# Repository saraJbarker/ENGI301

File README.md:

<h1>ENGI301</h1>
Repository for ENGI301 course work
<h3>Project 1</h3>
The project_1 folder contains the code for the PocketBeagle Medication Dispenser, found on my Hackster: https://www.hackster.io/sarajbarker/pocketbeagle-medication-dispenser-ca1f8f </br> </br>
All of the hardware can be found on the Hackster page. For the code, the only file needed is <a href=https://github.com/saraJbarker/ENGI301/blob/main/project_1/main_code3.py"">main_code3.py</a>. 
To set up and run this code: </br>
<ol>
  <li> Wire everything up according to the directions on Hackster (also see <a href="https://github.com/saraJbarker/ENGI301/blob/main/project_1/sketch_bb.png"> sketch_bb.png</a> for a Fritzing diagram) </li>
  <li> Connect the PocketBeagle to the internet </li>
  <li> Set up the PocketBeagle to run Python: 
    <ul>
      <li><code>sudo apt-get update </code></li>
      <li><code>sudo apt-get install build-essential python-dev python-setuptools python-smbus -y </code></li>
      <li><code>sudo apt-get install python-pip python3-pip -y</code></li>
    </ul>
  <li>Install Adafruit BBIO:
    <ul><code>sudo pip3 install --upgrade Adafruit_BBIO</code></ul>
    </li>
  <li>Drag and drop <a href=https://github.com/saraJbarker/ENGI301/blob/main/project_1/main_code3.py>main_code3.py</a> into your PocketBeagle directory.</li>
  <li>Press "Run".</li>
  </ol>
  </br>
  Included in the Project 1 folder are the STL and Solidworks files for the pillbox - the STL can go into a 3D printing software like 3DprinterOS, or you can modify the Solidworks file and make a new STL file. <a href="https://github.com/saraJbarker/ENGI301/blob/main/project_1/boxv3all.ai">boxv3all.ai</a> is the Illustrator file for the sides of the wooden box. This can be used with a laser cutter to cut the wood out. <a href="https://github.com/saraJbarker/ENGI301/blob/main/project_1/sketch_bb.png">sketch_bb.png</a> is a picture of the Fritzing file. <code>code_skeleton</code>, <code>main_code.py</code>, and <code>main_code2.py</code> are just in progress versions of the currently updated code, <code>main_code3.py</code> - there isn't a need to download these.
  <h3>Project 2</h3>
  The project_2 folder contains files for a PCB that would control the medication dispenser described in Project 1. The library, schematic, and board files in EAGLE are included in the EAGLE subfolder, and the Gerber files are in the MFG subfolder. If you would like to make this PCB, you will need to send the Gerber files to a manufacturer. There is also a PDF version of the schematic and a Bill of Materials inside the project_2 folder. </br>
  <i>Note:</i> the PCB has not been physically made, so there may be errors in the provided files.

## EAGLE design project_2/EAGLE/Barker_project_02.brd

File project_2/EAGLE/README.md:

This is the folder for all EAGLE files for the PCB.

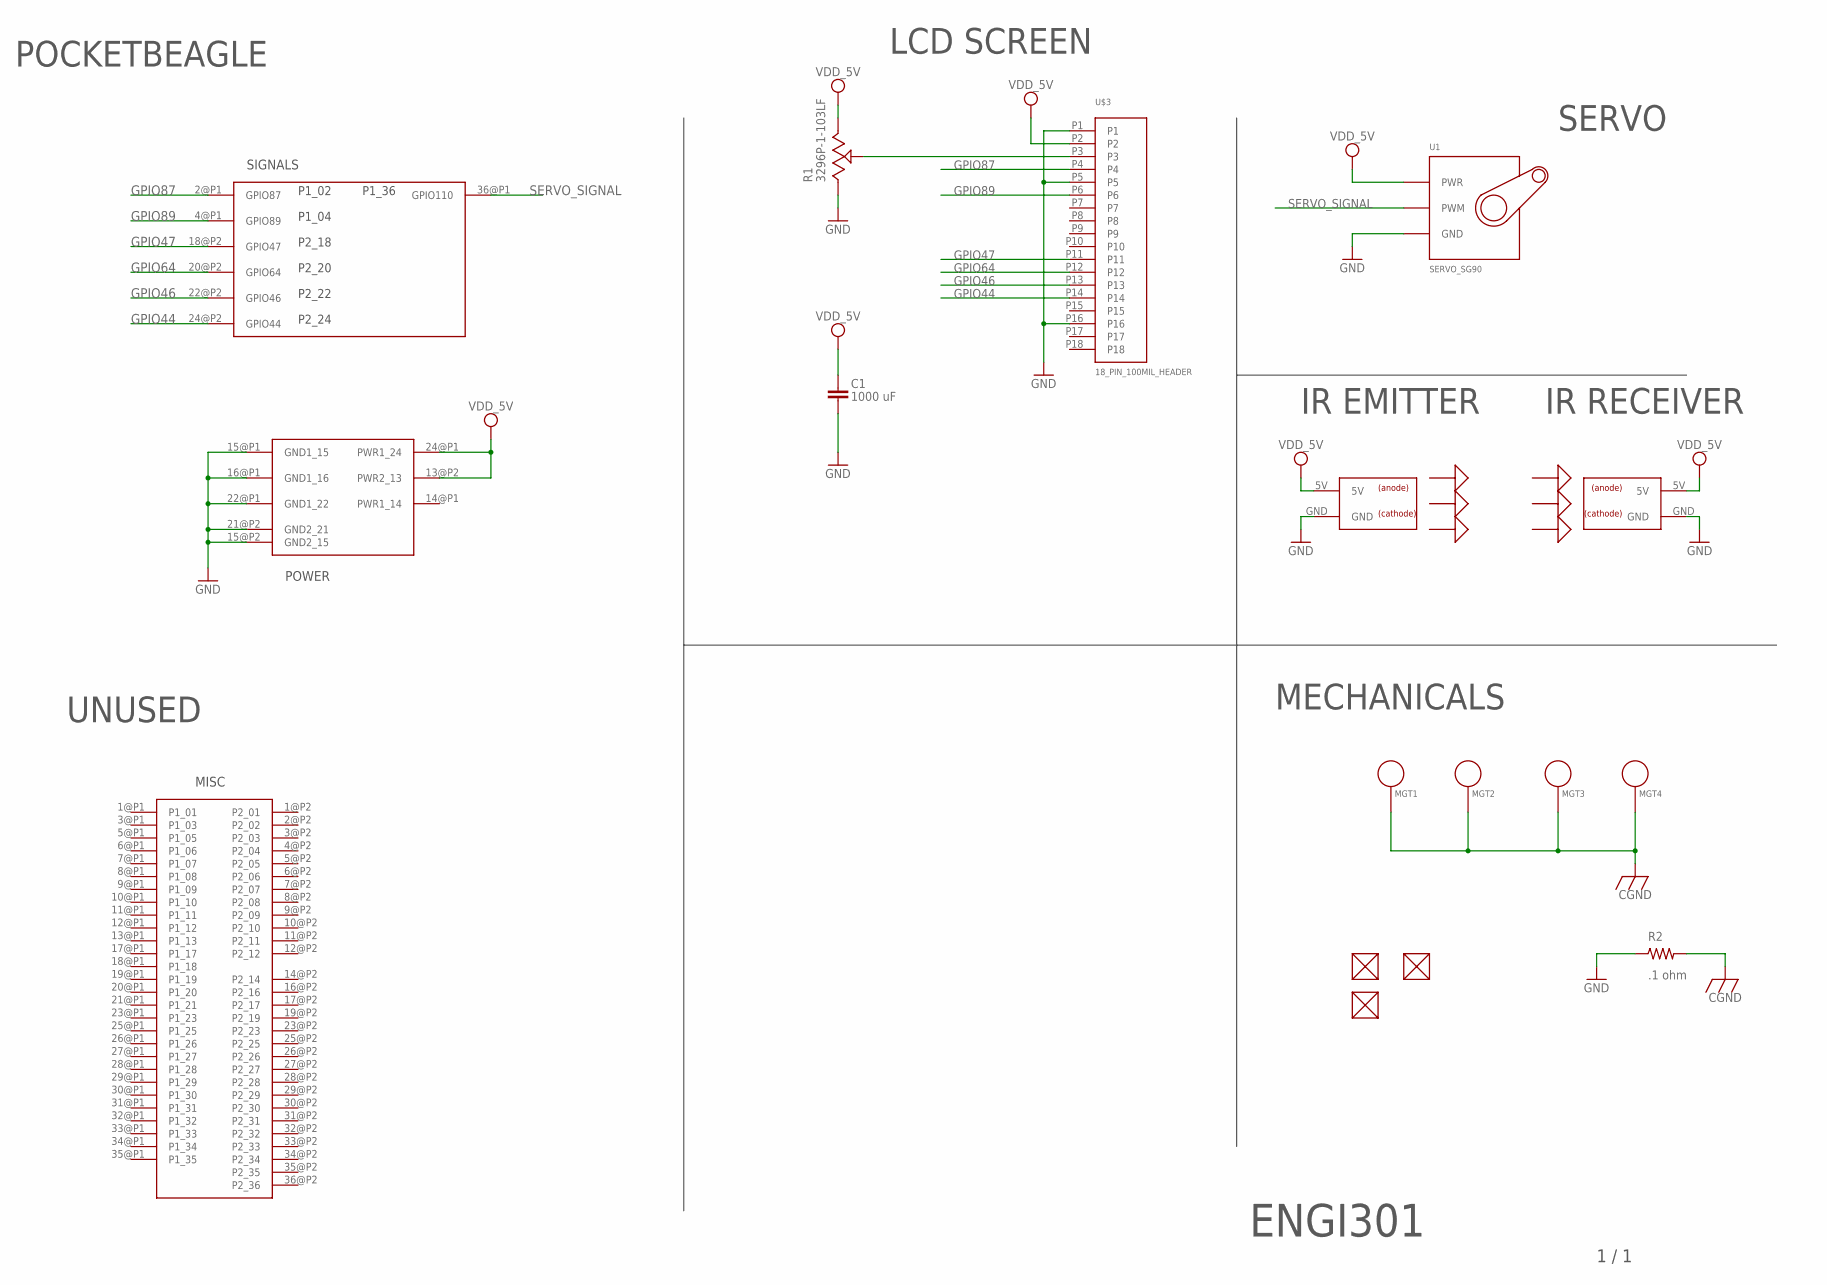
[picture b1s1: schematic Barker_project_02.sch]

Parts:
C1: 1000 uF; C0402
FUD1, FUD2, FUD3: FIDUCIAL; FIDUCIAL_40MIL
MGT1, MGT2, MGT3, MGT4: MOUNTING_HOLE
R1: 3296P-1-103LF; TRIM_3296P-1-103LF
R2: .1 ohm; R0402
U1: SERVO_SG90; SERVO-X1
U2: POCKETBEAGLE
U3: IR_EMITTER; 2_PIN_100MIL_HEADER
U4: IR_DETECTOR; 2_PIN_100MIL_HEADER
U$3: 18_PIN_100MIL_HEADER

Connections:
CGND: MGT1.P$1, MGT2.P$1, MGT3.P$1, MGT4.P$1, R2.2
GND: C1.2, R1.1 (CCW), R2.1, U1.GND, U2.15@P1 (GND1_15), U2.15@P2 (GND2_15), U2.16@P1 (GND1_16), U2.21@P2 (GND2_21), U2.22@P1 (GND1_22), U3.GND, U4.GND, U$3.P1, U$3.P5, U$3.P16
GPIO44: U2.24@P2 (GPIO44), U$3.P14
GPIO46: U2.22@P2 (GPIO46), U$3.P13
GPIO47: U2.18@P2 (GPIO47), U$3.P11
GPIO64: U2.20@P2 (GPIO64), U$3.P12
GPIO87: U2.2@P1 (GPIO87), U$3.P4
GPIO89: U2.4@P1 (GPIO89), U$3.P6
unnamed: R1.2 (WIPER), U$3.P3
SERVO_SIGNAL: U1.SIG (PWM), U2.36@P1 (GPIO110)
VDD_5V: C1.1, R1.3 (CW), U1.PWR, U2.13@P2 (PWR2_13), U2.24@P1 (PWR1_24), U3.5V, U4.5V, U$3.P2

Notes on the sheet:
IR RECEIVER
IR EMITTER
SERVO
LCD SCREEN
POCKETBEAGLE
MECHANICALS
POWER
SIGNALS
MISC
ENGI301
1 / 1
UNUSED

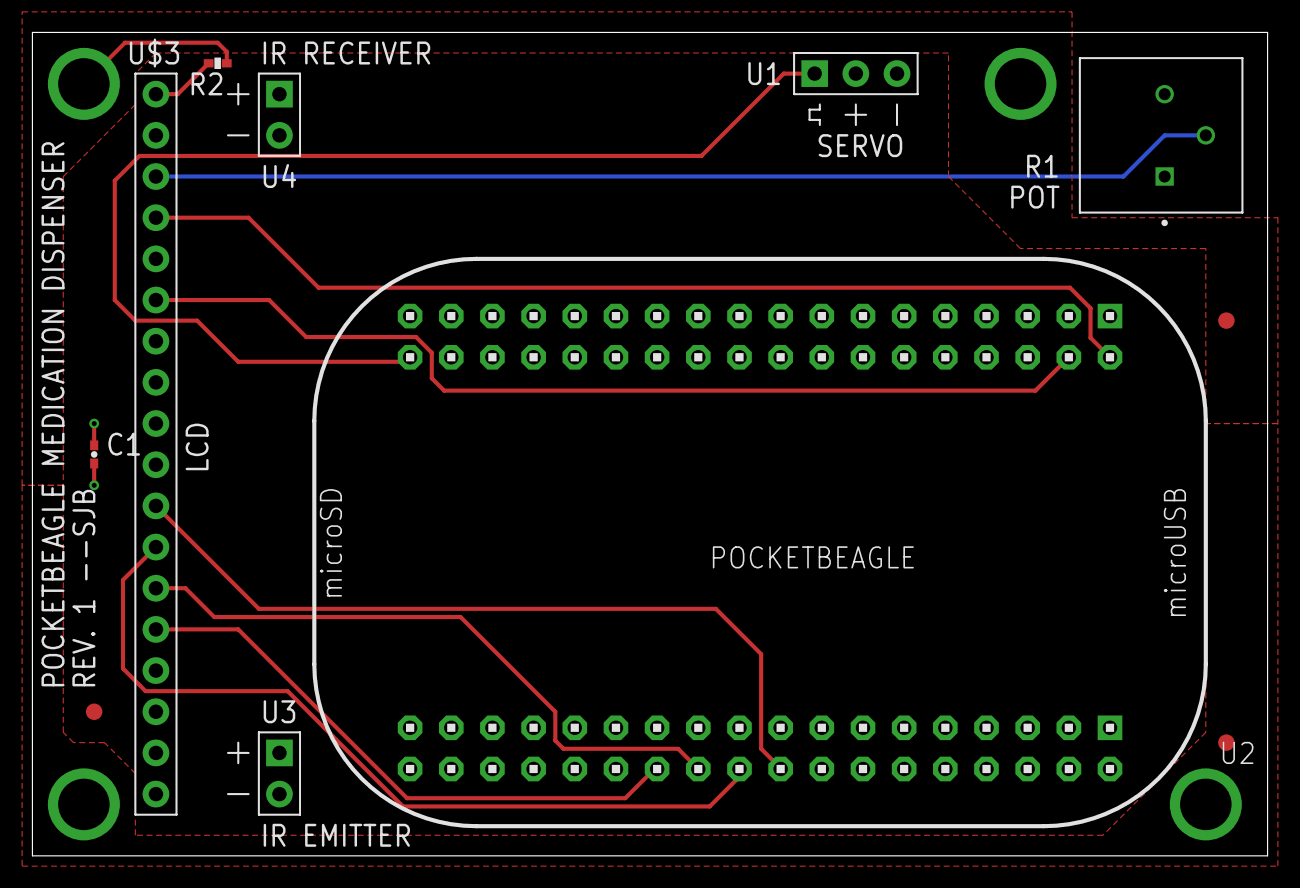
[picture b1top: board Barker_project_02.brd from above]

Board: 4 copper layers, 76.2 x 50.8 mm, 15 parts (0 on the bottom side), 11 nets.

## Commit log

2022-02-01 Updating README.md
2022-02-15 Added simple calc original code
2022-02-15 Create simple_calc
2022-02-15 Added Python 2 functionality, right and left shift, modulus, and exponentiation support.
2022-02-15 Add functionalities
2022-02-15 Add blink_USR3 file.
2022-02-15 Create simple_calc_modified
2022-02-15 Create simple_calc_original
2022-03-28 Add STL and Solidworks files for pill boxes
2022-03-30 Added skeleton of main code
2022-03-30 Added Solidworks and STL files for pill boxes
2022-04-01 Added Illustrator file for box
2022-04-01 Add update to main code
2022-04-05 Changed name to avoid confusion
2022-04-05 Added latest iteration of code
2022-04-05 Add latest iteration of code
2022-04-06 Update Readme (in progress)
2022-04-06 Added Fritzing diagram
2022-04-06 Small change to Readme
2022-04-27 Added project proposal presentation
2022-05-04 Add Bill of Materials
2022-05-04 Added Library file
2022-05-04 Added Board and Schematic files
2022-05-04 Added Schematic and Board files
2022-05-04 Added Gerber files
2022-05-04 Added pictures of top and bottom of board
2022-05-04 Added pictures of top and bottom layers
2022-05-04 Added schematic PDF
